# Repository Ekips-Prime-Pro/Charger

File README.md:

# Charger

This is the PCB of the Charger for Spike Prime batteries

## Table of Content

1. [Why exists this project?](#Why)
2. [How did we accomplish this?](#How)
3. [What do you Need to do it yourself?](#What)
4. [Guide for you to replicate this.](#Guide)

## Why

First of all we are two ex students from the First Lego League Team [PaRaMeRoS](https://www.parameros.net).
There we encountered the problem on why we are doing this:
Our Spike Prime died on us right before an event so we used it as a charger to don't waste money.
But all of a sudden it died completely up to the point where nothing worked.
Then we desieded that we had to do it our selfs to stay prepared for our contests.
Also we thought that we could build a few of them so we can charde our Spike Batteries parallel.

## How

First of all we searched online for the limited [datasheets](https://github.com/Ekips-Prime-Pro/Charger/blob/5f66ce05a6301ec8a03dad4ef41c37c246556ab5/Material/SPIKE_Prime_Battery_Tech_Spec_Sheet.pdf) from Lego(Thanks Lego),
after that we created a Collection of all the important Information that we had.
With that information we continued by sesrching for a PCB programm in that process we
decided to use [KiCad](https://www.kicad.org). There we started by placing the input and the 
Output for the Batterie(7,3V/1A) and the Barrel Jack(12v/2A). We considerd the differenz
for the input and the output of the PCB.
Form that we build a plan for regulating the voltage and then using an battery charging 
regulator in our case an 12-7,3 V /1A Voltage Regulator [LM317-POT-128]() and the Charging 
regulator [MCP73831-OT-23](https://github.com/Ekips-Prime-Pro/Charger/blob/5f66ce05a6301ec8a03dad4ef41c37c246556ab5/Material/MCP73831-Family-Data-Sheet-DS20001984H.pdf). 
Then we looked at the Datasheets of the CMD's and connected them for the Chip appropriate.

## What

To Assemble it your self you need:
1. A copy of the pcb
2. all of the parts in the [parts list](#)
3. A heatgun and a soldering iron
4. Soldering paste

## Guide

First you have to download the 

## Sumary

Over all the PCB is for those that are interested in learning about the Spike Prime Environment.
If you don't have any experience you should not replicate this.
Some more interesting information are:
Lego isn't our friend.

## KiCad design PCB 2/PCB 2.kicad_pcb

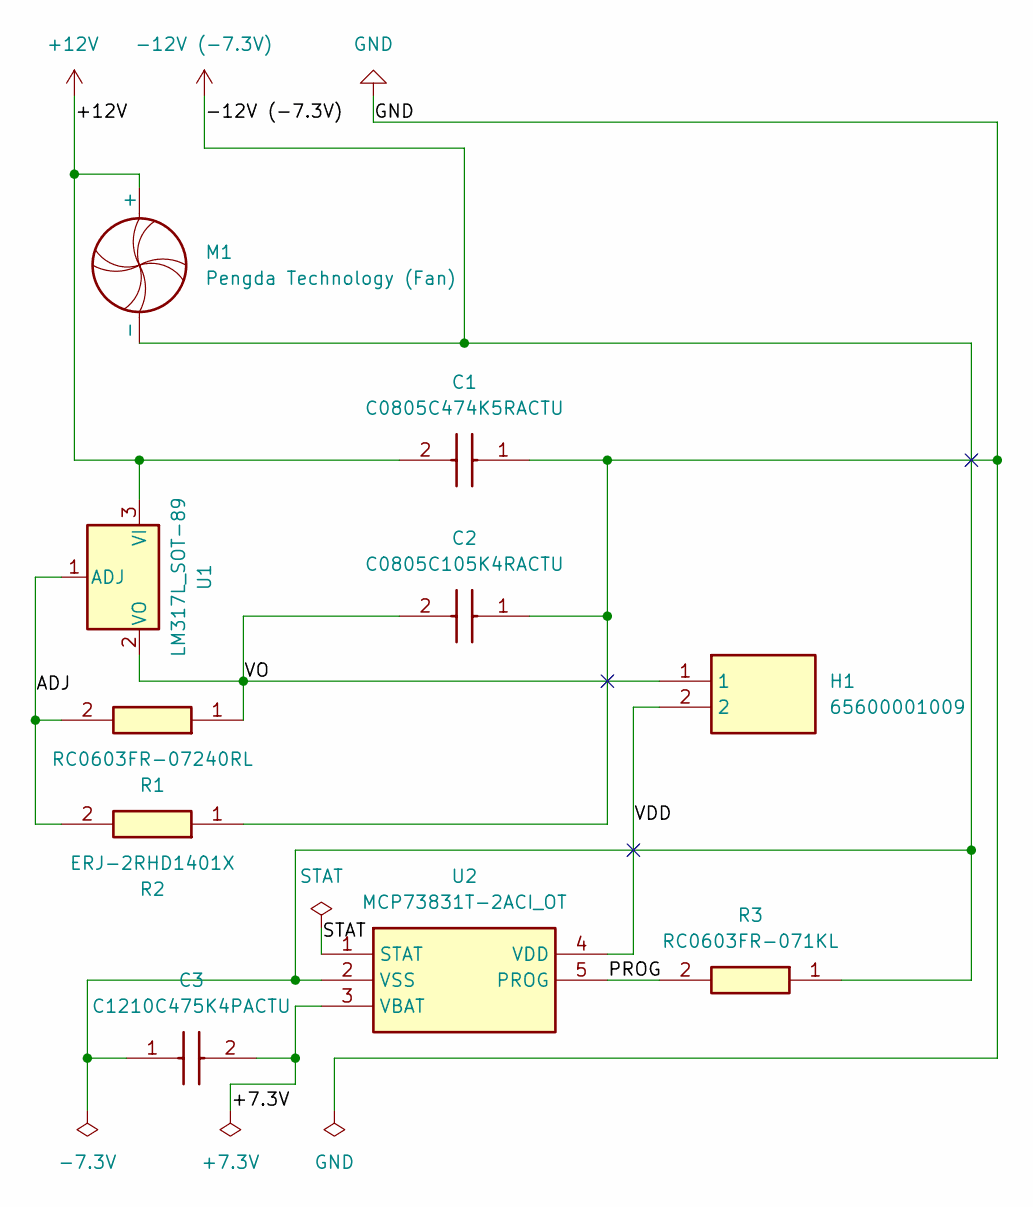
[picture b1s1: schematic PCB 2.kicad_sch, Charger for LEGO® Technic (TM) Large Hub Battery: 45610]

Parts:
C1: C0805C474K5RACTU; C_0805_2012Metric_Pad1.18x1.45mm_HandSolder; Mouser Part Number 80-C0805C474K5R
C2: C0805C105K4RACTU; C_0805_2012Metric_Pad1.18x1.45mm_HandSolder; Mouser Part Number 80-C0805C105K4R
C3: C1210C475K4PACTU; C_1210_3225Metric_Pad1.33x2.70mm_HandSolder; Mouser Part Number 80-C1210C475K4P
H1: 65600001009; Mouser Part Number 576-65600001009
M1: Pengda Technology (Fan)
R1: RC0603FR-07240RL; R_0603_1608Metric_Pad0.98x0.95mm_HandSolder; Mouser Part Number 603-RC0603FR-07240RL
R2: ERJ-2RHD1401X; R_0402_1005Metric_Pad0.72x0.64mm_HandSolder; Mouser Part Number 667-ERJ-2RHD1401X
R3: RC0603FR-071KL; R_0603_1608Metric_Pad0.98x0.95mm_HandSolder; Mouser Part Number 603-RC0603FR-071KL
U1: LM317L_SOT-89; SOT-89-3
U2: MCP73831T-2ACI_OT; SOT-23-5_HandSoldering; Mouser Part Number 579-MCP73831T-2ACIOT

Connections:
+12V: C1.2, M1.1 (+), U1.3 (VI)
-12V (-7.3V): C3.1, M1.2 (-), R3.1, U2.2 (VSS)
/+7.3V: C3.2, U2.3 (VBAT)
/ADJ: R1.2, R2.2, U1.1 (ADJ)
/PROG: R3.2, U2.5 (PROG)
/STAT: U2.1 (STAT)
/VDD: H1.2, U2.4 (VDD)
/VO: C2.2, H1.1, R1.1, U1.2 (VO)
GND: C1.1, C2.1, R2.1

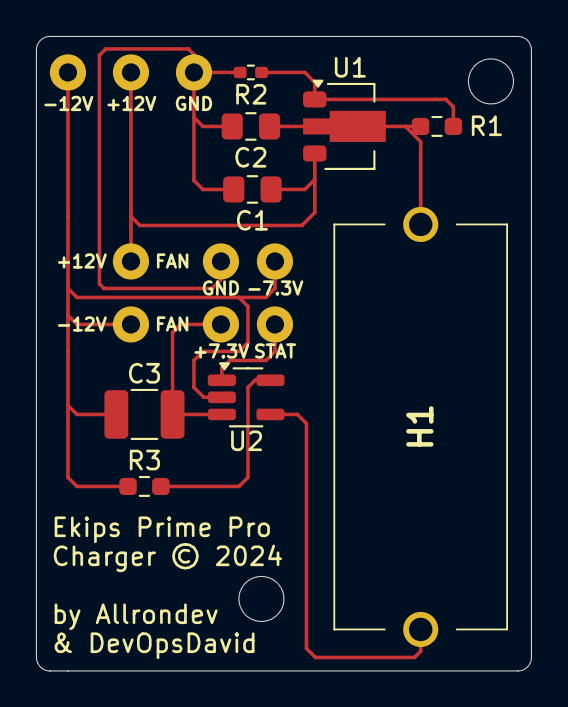
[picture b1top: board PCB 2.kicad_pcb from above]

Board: 2 copper layers, 27.5 x 35.2 mm, 9 parts (0 on the bottom side), 8 nets.

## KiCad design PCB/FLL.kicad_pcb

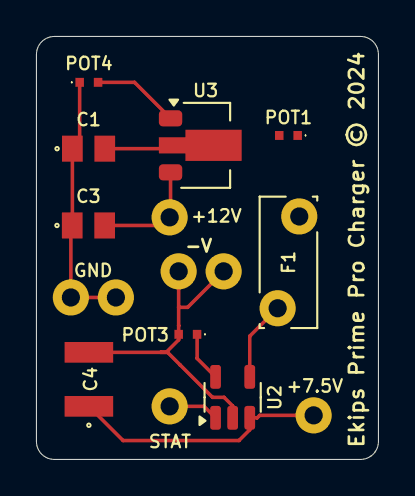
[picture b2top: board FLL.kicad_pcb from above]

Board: 2 copper layers, 19.0 x 23.5 mm, 9 parts (0 on the bottom side), 8 nets.

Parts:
C1: 1uF; C0805
C3: 0,47uF; C0805
C4: 4,7uF; C1210
F1: Polyfuse; Fuse_Bourns_MF-RG300
POT1: 240Ω; ERJ2RKD1004X
POT3: 1kΩ; ERJ2RKD1004X
POT4: 1,4kΩ; ERJ2RKD1004X
U2: MCP73831-2-OT; SOT-23-5
U3: LM317L_SOT-89; SOT-89-3

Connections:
+7.5V: C4.1, U2.3 (V_{BAT})
-7.5V: C4.2, POT3.2, U2.2 (V_{SS})
GND: C1.1, C3.1, POT4.1
unnamed: C3.2, U3.3 (VI)
unnamed: POT3.1, U2.5 (PROG)
unnamed: F1.2, U2.4 (V_{DD})
unnamed: POT4.2, U3.1 (ADJ)
unnamed: C1.2, F1.1, U3.2 (VO)

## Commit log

2024-07-05 chore: Remove unnecessary files and update PCB design configuration
2024-07-05 chore: Update PCB design configuration and remove unnecessary files
2024-07-06 Update PCB design configuration and net colors
2024-07-06 Added Pics
2024-07-06 added official Lego Spec Sheet for Battery
2024-07-09 deleted: PCB/FLL-backups/FLL-2024-07-08_080917.zip
    new file: PCB/FLL-backups/FLL-2024-07-09_095727.zip
    new file: PCB/FLL-backups/FLL-2024-07-09_100644.zip
    modified: PCB/FLL.kicad_sch
2024-07-09 Update PCB design configuration and remove unnecessary files
2024-07-10 README.md aktualisieren
2024-07-10 Fixed URL Linking
2024-07-10 Fixed Wrong KiCad Link
2024-07-10 Added Mouser Electronics Parts
2024-07-11 Parts list
2024-07-11 chore: Remove unused KiCad symbol files
2024-07-11 chore: Update plot directory for KiCad project
2024-07-23 Rework ALL
2024-07-23 Added Output Pins
2024-07-23 Fotos

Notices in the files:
PCB 2/PCB 2.kicad_pcb:
Charger © 2024
PCB/FLL.kicad_pcb:
Ekips Prime Pro Charger © 2024
